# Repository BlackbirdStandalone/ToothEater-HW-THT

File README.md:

# ToothEater-HW-THT

This repository contains the hardware design of the Honda Blackbird v1.1 Tooth Eater Module - (Through hole version). This through hole version is intended for the DIY'er for easier construction. This PCB is a simple 2 layer design, measuring 44mm x 44mm for insertion into the Hammond 1551R case.<br /><br />
This hardware is designed to work with the latest firmware version (v1.x) contained in the firmware respository. I.e. <i>'ToothEater_v1.2.hex'.</i><br />
<br />
Shown below are blank boards as received by PCBWay. This is a small unit slightly larger than a matchbox, shown in the 2" x 2" case.

<table border="1">
<tr>

<td align="center" valign="center">

</img>
</td>

<td>

</img>
</td>

</tr>
</table>

<br />

A zoomed picture of the board is shown below. The full bill of materials can be found in the 'BOM' directory, however the table below will quickly identify the components. This table reflects the BOM for PCB v1.1.

<table border="3">
<tr>
<td align="center" valign="center"><b><u>Component</u></b></td>
<td align="center" valign="center"><b><u>Value</u></b></td>
</tr>

<tr>
<td align="center" valign="center">U1</td>
<td align="center" valign="center">atTiny85 microcontroller</td>
</tr>

<tr>
<td align="center" valign="center">U2</td>
<td align="center" valign="center">VR conditioner plug-in module (speeduino compatible)</td>
</tr>

<tr>
<td align="center" valign="center">U3</td>
<td align="center" valign="center">MCP100 reset chip</td>
</tr>

<tr>
<td align="center" valign="center">Q1</td>
<td align="center" valign="center">BD681</td>
</tr>

<tr>
<td align="center" valign="center">D1</td>
<td align="center" valign="center">1N4004</td>
</tr>

<tr>
<td align="center" valign="center">D2</td>
<td align="center" valign="center">6.2v zener</td>
</tr>

<tr>
<td align="center" valign="center">C1, C2</td>
<td align="center" valign="center">100n</td>
</tr>

<tr>
<td align="center" valign="center">R1</td>
<td align="center" valign="center">1K5</td>
</tr>

<tr>
<td align="center" valign="center">R2</td>
<td align="center" valign="center">470</td>
</tr>

<tr>
<td align="center" valign="center">R3,R5</td>
<td align="center" valign="center">10K</td>
</tr>

<tr>
<td align="center" valign="center">R4,R6</td>
<td align="center" valign="center">1K</td>
</tr>

<tr>
<td align="center" valign="center">R7,R9</td>
<td align="center" valign="center">47K</td>
</tr>

<tr>
<td align="center" valign="center">R11</td>
<td align="center" valign="center">4K7</td>
</tr>

<tr>
<td align="center" valign="center">R8,R10,R12</td>
<td align="center" valign="center">330</td>
</tr>

<tr>
<td align="center" valign="center">Q2,Q3,Q4,Q5,Q6</td>
<td align="center" valign="center">BC546B</td>
</tr>

<tr>
<td align="center" valign="center">D3</td>
<td align="center" valign="center">Power Led - Red (standard 3mm spacing)</td>
</tr>

<tr>
<td align="center" valign="center">D4,D5</td>
<td align="center" valign="center">Crank and cam Leds - Yellow (standard 3mm spacing)</td>
</tr>

<tr>
<td align="center" valign="center">J1,J2</td>
<td align="center" valign="center">Molex Micro-Fit 3.0 43045 </td>
</tr>

</table>

</img>

<br /><br />
The board is shown below with the components assembled.

</img>

<br />

<table border="1">

The following illustrates different views of the v1.1 assembled board (without the VR mini-board installed).<br />

<tr>
<td align="center" valign="center">

</img>
</td>
<td>

</img>
</td>
</tr>

<tr>
<td align="center" valign="center">

</img>
</td>
<td>

</img>
</td>
</tr>

</table>

<table border="1">
<tr>

<br /><br />
The board is shown below with two mini wiring harnesses connected to it, along with the speeduino compatible VR plug in mini board.

<td align="center" valign="center">

</img>
</td>

</tr>
</table>

<br /><br />
Once the VR board is inserted into the tooth eater module, it may sit to tall such that it will not allow the lid to close on the case. This is due to the height of the two female 4x1 headers (8.5mm height) that is sits within. To remedy this, the plastic stand-offs may be pryed off with a screwdriver or similar. This will allow the VR module to sink lower into the tooth eater board once it is inserted.

</img>

<br />
Afterwards it will sit as follows. The overall height will now allow the package to fit within the case.

</img>

<br /><br />
When assembled, the BD681 transistor sits slightly proud of the case top (~2mm). This can be fixed by bending it to the left as shown.

</img>

</img>

<br /><br />
The connectors require a section to be cut out of the case.

</img>

</img>

<br /><br />
The board is fitted to the case and relative size is shown.

</img>

</img>

<br /><br />

<table border="3">
<tr>
<td>
<p style="text-align: left;">The final connections are shown as follows:</p>
</td>
</tr>

<tr>
<td>

</img>
</td>
</tr>

<tr>
<td>
<p>The board requires +12v and a ground connection. These can be tapped off the wires that feed your ECU.</p>
</td>
</tr>

<tr>
<td>
The inputs to this module are:
<ul>
  <li> CRANK VR+ (from the bikes wiring harness) </li>
  <li> CAM VR+ (from the bikes wiring harness) </li>
  <li> VR- (shared with both crank & cam VR- on the bikes wiring harness) </li>
</ul>
</td>
</tr>

<tr>
<td>
The outputs are:
<ul>
  <li>CAM TTL (0-4.1v level single cam pulse - fed into your downstream ECU)</li>
  <li>CRANK TTL (0-4.1v level single crank pulse - fed into your downstream ECU)</li>
  <li>TACHO (0-12v level square wave - fed to your dash via pin A19 on main wiring harness)</li>
</ul>
</td>
</tr>

<tr>
<td>
<p>Notes:<br />
1. The crank signal is the 12 pulses per crank rotation. The cam signal is post-processed by the tooth eater, therefore 1 cam pulse per engine cycle (I.e. Two crank revolutions, 720 deg).<br /><br />
2. The TTL output voltages are square wave outputs. The output voltage is slightly less than 5.0v and realistically closer to 4.1v. This should be fine in practice for ECUs expecting either 5.0v or 3.3v inputs (with internal built in protection on its inputs). In the future on the next board revision, I may add a jumper and a voltage divider to offer both use cases.<br />
</p>
</td>
</tr>

</table>

<br />

## Additional notes to observe

1. If you are using the speeduino compatible VR conditioner mini board by 'OpenLogic EFI', then you will need to solder both VR1 and VR2 jumpers as shown in the image below. This is so your crank and cam signals can be processed by the tooth eater.
2. There are also additional jumpers on the underside of the board. If you are using the VR board as mentioned above then leave these open circuit (o.c) as they are. These jumpers are of no practial use on the bike. <br />
The purpose of these jumpers are mainly for bench testing the board with 0-5v TTL signals when testing with ardu-stim, so they should only be soldered when bench testing or when HALL effect sensors are being used instead of the VR.
<table border="1">
<tr>

<td align="center" valign="center">

</img>
</td>

<td>

</img>
</td>

</tr>
</table>

<br /><br />

# Hardware Design

<table border="1">

<tr> 
<td width="20%">
<strong><u>Current Revision</u></strong>
</td>
<td width="60%">
<strong><u>Date</u></strong>
</td>
<td width="20%">
<strong><u>Author</u></strong>
</td>
</tr>

<tr>
<td width="20%">
v1.1
</td>
<td width="60%">
July 2026
</td>
<td width="20%">
Alex Kiaos
</td>
</tr>

</table>

<br />
This project has been designed in Kicad 6.0.11 under linux and is licenced under the CERN Open Hardware Licence Version 2 - Strongly Reciprocal (CERN-OHL-S).<br /><br />

The directory structure of this project is as follows:

<table border="1">

<tr> 
<td width="20%">
<strong><u>Directory</u></strong>
</td>
<td width="80%">
<strong><u>Description</u></strong>
</td>
</tr>

<tr>
<td width="20%">
BOM
</td>
<td width="80%">
Bill of materials
</td>
</tr>

<tr>
<td width="20%">
kicad
</td>
<td width="80%">
The main project file is 'ToothEater.kicad_pro' found under</br>'/pcb/kicad/ToothEater'.</br></br>
Gerber files can be found as a group of 9 individual files under the 'gerbers' directory or as a single zipped file under the 'gerber_zipped' directory for uploading to a PCB house for manufacture.</br></br>
The 'CustomLibrary' directory contains the custom symbols and footprints used in the project.
</td>
</tr>

</table>

</br>
After cloning the repository and opening the project for the first time, you may need to set up the symbol library path.<br />

To setup the symbols library, in the menu:<br>
<pre><i>Preferences -> Manage Symbol Libraries</i><br>
  Then in the 2nd tab under 'Project specific libraries' add the following:<br>
Nickname: <b>ToothEater</b><br>
Library Path: <b>${KIPRJMOD}/../CustomLibrary/symbols/ToothEater_symbols.kicad_sym</b><br>
</pre>
<br><br>

# Relevant links

### PCBWay
To visit the PCBWay project and/or place an [order](https://www.pcbway.com/project/shareproject/Honda_CBR_Tooth_Eater_Module_Compatibility_module_for_the_CBR_1100XX_Super_Bla_bf3a4c0d.html).

### Wiring Harness & Pinouts
To see the ECU pin-out details, refer to the latest pdf file at: 
[Wiring Harness Pinout diagram](https://github.com/BlackbirdStandalone/Documentation/tree/main/wiring).

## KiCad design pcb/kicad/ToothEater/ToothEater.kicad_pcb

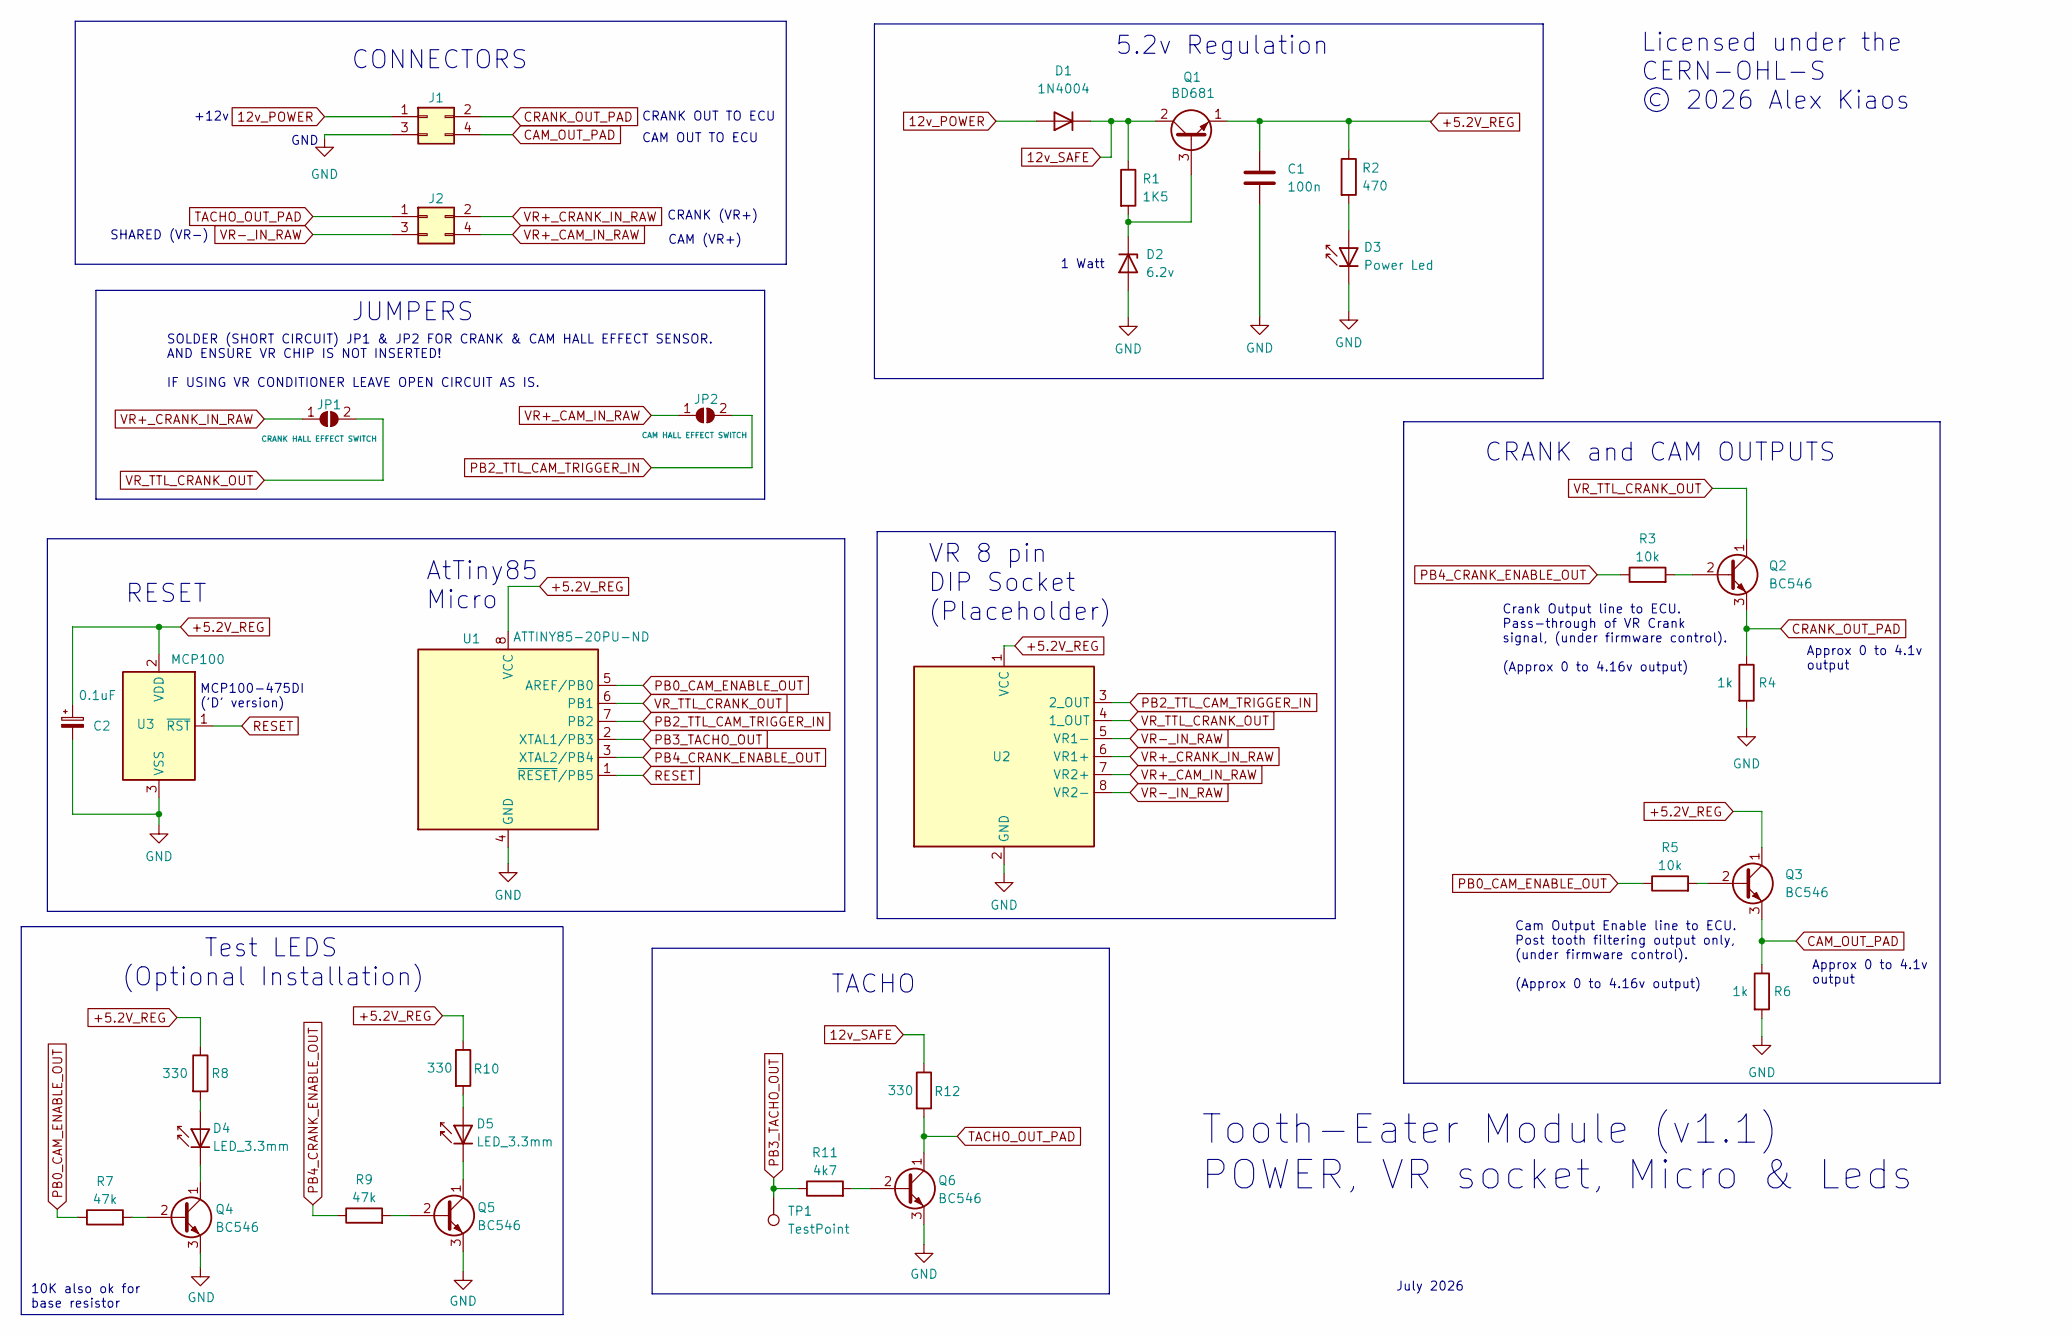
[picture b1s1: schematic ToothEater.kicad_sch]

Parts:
C1: 100n; C_Rect_L7.0mm_W4.5mm_P5.00mm
C2: 0.1uF; C_Axial_L3.8mm_D2.6mm_P7.50mm_Horizontal
D1: 1N4004; D_DO-41_SOD81_P10.16mm_Horizontal
D2: 6.2v; D_DO-41_SOD81_P10.16mm_Horizontal
D3: Power Led; LED_D3.0mm_IRBlack
D4, D5: LED_3.3mm; LED_D3.0mm_IRBlack
J1, J2: Conn_02x02_Molex; Molex_Micro-Fit_3.0_43045-0400_2x02_P3.00mm_Horizontal
JP1: CRANK HALL EFFECT SWITCH; SolderJumper-2_P1.3mm_Open_RoundedPad1.0x1.5mm
JP2: CAM HALL EFFECT SWITCH; SolderJumper-2_P1.3mm_Open_RoundedPad1.0x1.5mm
Q1: BD681; SIPAK_Vertical
Q2, Q3, Q4, Q5, Q6: BC546; TO-92_Inline
R1: 1K5; R_Axial_DIN0207_L6.3mm_D2.5mm_P10.16mm_Horizontal
R2: 470; R_Axial_DIN0207_L6.3mm_D2.5mm_P2.54mm_Vertical
R3, R5: 10k; R_Axial_DIN0207_L6.3mm_D2.5mm_P10.16mm_Horizontal
R4, R6: 1k; R_Axial_DIN0207_L6.3mm_D2.5mm_P10.16mm_Horizontal
R7, R9: 47k; R_Axial_DIN0207_L6.3mm_D2.5mm_P2.54mm_Vertical
R8, R10, R12: 330; R_Axial_DIN0207_L6.3mm_D2.5mm_P2.54mm_Vertical
R11: 4k7; R_Axial_DIN0207_L6.3mm_D2.5mm_P2.54mm_Vertical
TP1: TestPoint; TestPoint_Pad_1.0x1.0mm
U1: ATTINY85-20PU-ND; DIP-8_W7.62mm_Socket_LongPads
U2: VR_Conditioner_8-Pin-DIP; DIP-8_W7.62mm
U3: MCP100; TO-92_Inline

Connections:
12v_POWER: D1.2 (A), J1.1
12v_SAFE: D1.1 (K), Q1.2 (C), R1.1, R12.1
+5.2V_REG: C1.1, C2.1, Q1.1 (E), Q3.1 (C), R2.1, R8.1, R10.1, U1.8 (VCC), U2.1 (VCC), U3.2 (VDD)
CAM_OUT_PAD: J1.4, Q3.3 (E), R6.1
CRANK_OUT_PAD: J1.2, Q2.3 (E), R4.1
GND: C1.2, C2.2, D2.2 (A), D3.1 (K), J1.3, Q4.3 (E), Q5.3 (E), Q6.3 (E), R4.2, R6.2, U1.4 (GND), U2.2 (GND), U3.3 (VSS)
unnamed: D2.1 (K), Q1.3 (B), R1.2
unnamed: D3.2 (A), R2.2
unnamed: D4.1 (K), Q4.1 (C)
unnamed: D4.2 (A), R8.2
unnamed: D5.1 (K), Q5.1 (C)
unnamed: D5.2 (A), R10.2
unnamed: Q2.2 (B), R3.2
unnamed: Q3.2 (B), R5.2
unnamed: Q4.2 (B), R7.2
unnamed: Q5.2 (B), R9.2
unnamed: Q6.2 (B), R11.2
PB0_CAM_ENABLE_OUT: R5.1, R7.1, U1.5 (AREF/PB0)
PB2_TTL_CAM_TRIGGER_IN: JP2.2 (B), U1.7 (PB2), U2.3 (2_OUT)
PB3_TACHO_OUT: R11.1, TP1.1, U1.2 (XTAL1/PB3)
PB4_CRANK_ENABLE_OUT: R3.1, R9.1, U1.3 (XTAL2/PB4)
RESET: U1.1 (~RESET/PB5), U3.1 (~RST)
TACHO_OUT_PAD: J2.1, Q6.1 (C), R12.2
VR+_CAM_IN_RAW: J2.4, JP2.1 (A), U2.7 (VR2+)
VR+_CRANK_IN_RAW: J2.2, JP1.1 (A), U2.6 (VR1+)
VR-_IN_RAW: J2.3, U2.5 (VR1-), U2.8 (VR2-)
VR_TTL_CRANK_OUT: JP1.2 (B), Q2.1 (C), U1.6 (PB1), U2.4 (1_OUT)

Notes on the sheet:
CAM OUT TO ECU
CAM (VR+)
Licensed under the CERN-OHL-S © 2026 Alex Kiaos
+12v
CRANK (VR+)
Approx 0 to 4.1v output
VR 8 pin DIP Socket (Placeholder)
GND
CRANK and CAM OUTPUTS
5.2v Regulation
Tooth-Eater Module (v1.1) POWER, VR socket, Micro & Leds
Crank Output line to ECU. Pass-through of VR Crank signal, (under firmware control). (Approx 0 to 4.16v output)
TACHO
CRANK OUT TO ECU
1 Watt
SOLDER (SHORT CIRCUIT) JP1 & JP2 FOR CRANK & CAM HALL EFFECT SENSOR. AND ENSURE VR CHIP IS NOT INSERTED! IF USING VR CONDITIONER LEAVE OPEN CIRCUIT AS IS.
10K also ok for base resistor
Cam Output Enable line to ECU. Post tooth filtering output only, (under firmware control). (Approx 0 to 4.16v output)
July 2026
JUMPERS
CONNECTORS
AtTiny85 Micro
SHARED (VR-)
Test LEDS (Optional Installation)
MCP100-475DI ('D' version)
RESET

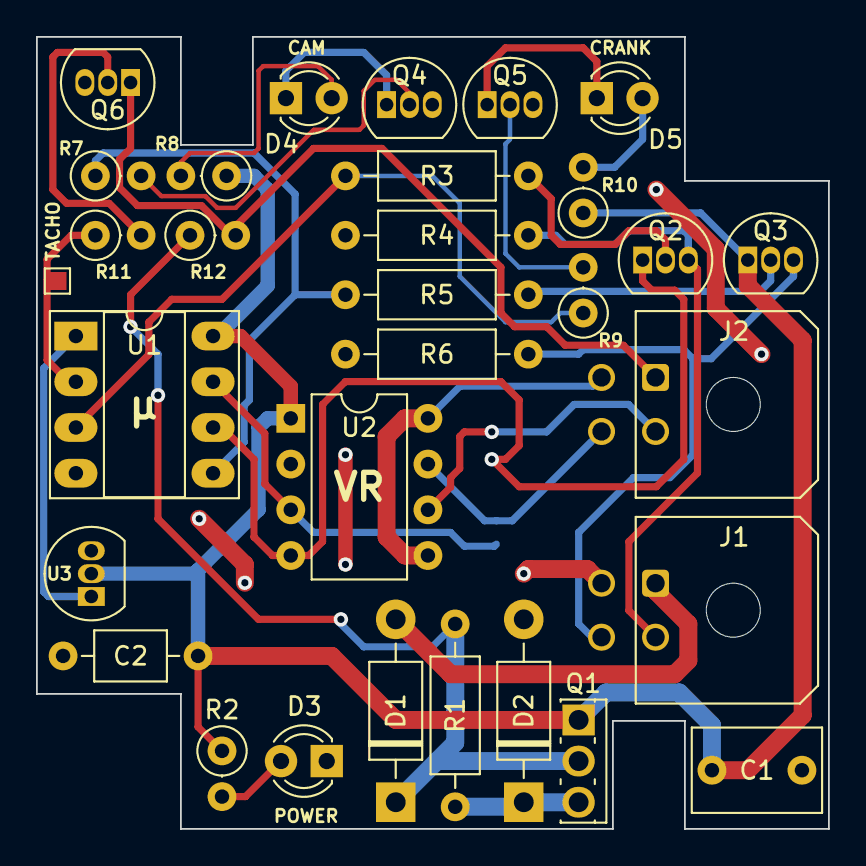
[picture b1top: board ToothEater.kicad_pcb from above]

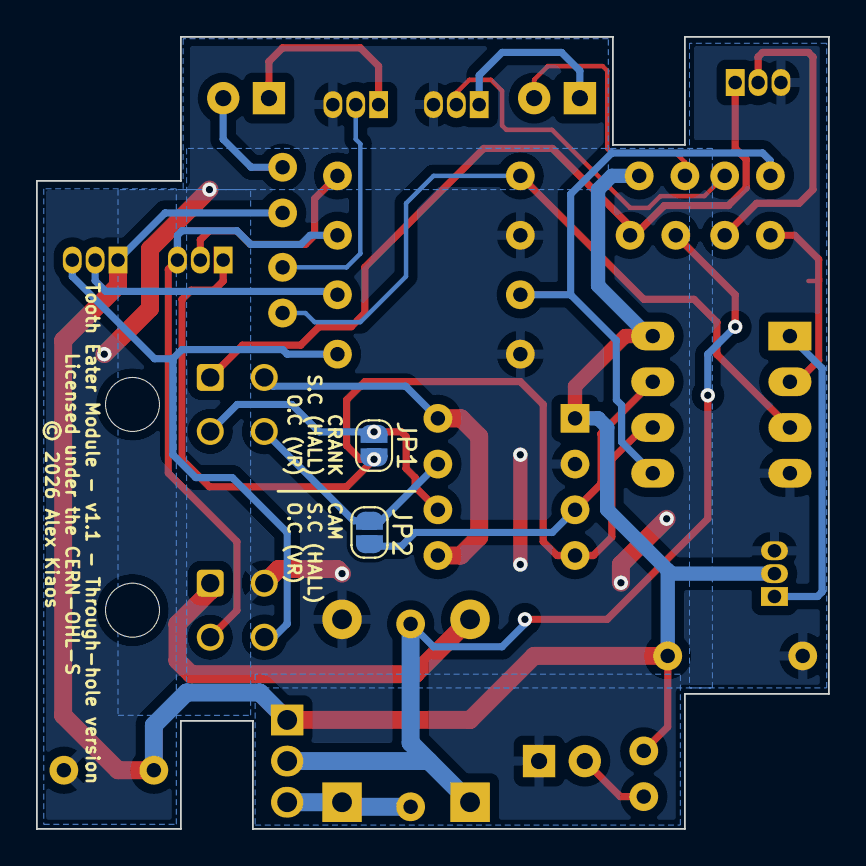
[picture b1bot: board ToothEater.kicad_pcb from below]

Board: 2 copper layers, 44.0 x 44.0 mm, 33 parts (2 on the bottom side), 27 nets.

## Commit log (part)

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2026-05-27 - PCB
2026-05-29 - Readme
